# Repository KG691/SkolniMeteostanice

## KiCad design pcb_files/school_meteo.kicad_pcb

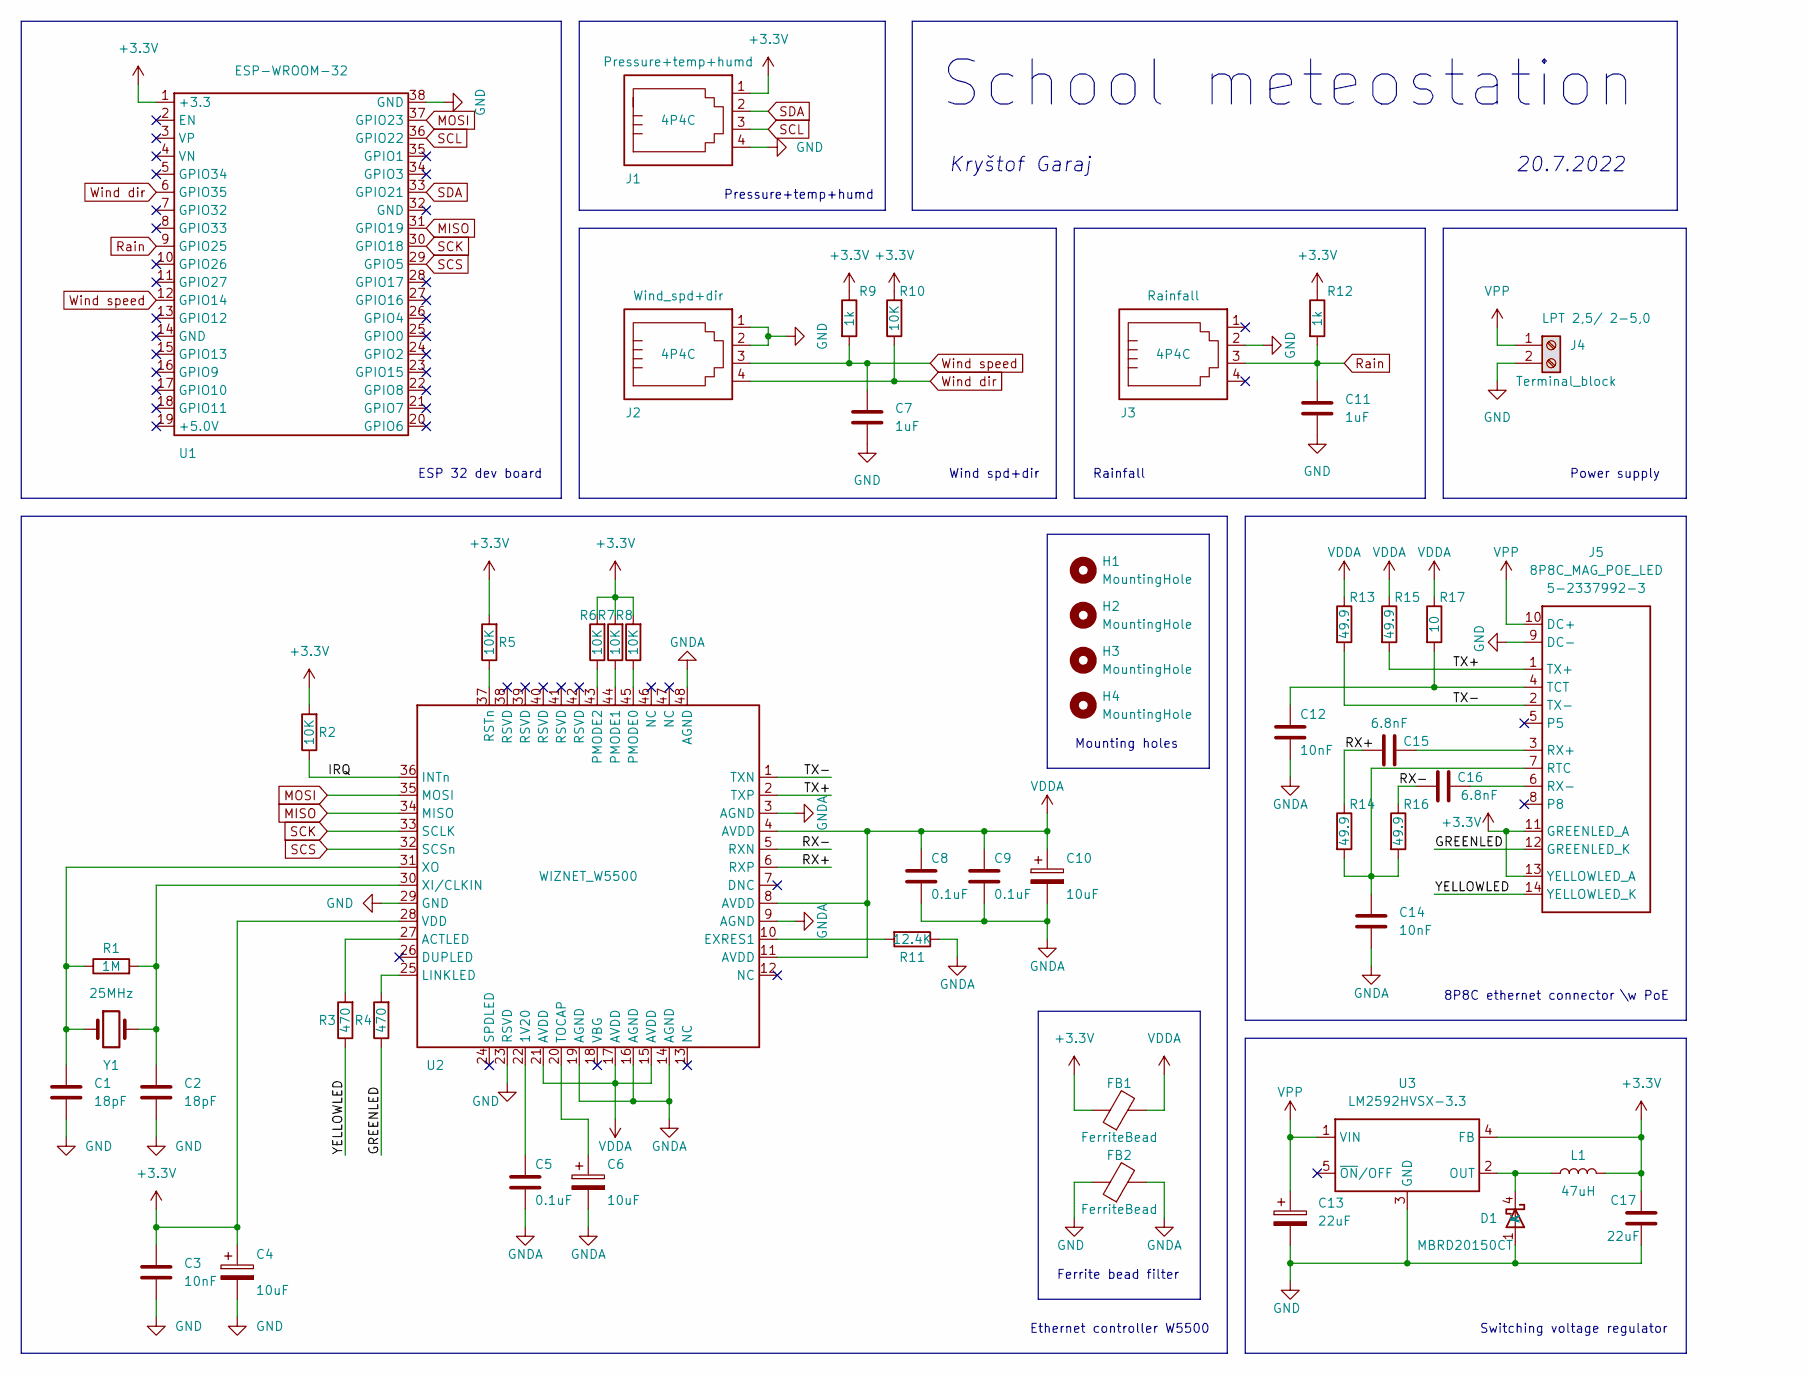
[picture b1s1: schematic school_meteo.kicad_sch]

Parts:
C1, C2: 18pF; C_Rect_L4.6mm_W3.0mm_P2.50mm_MKS02_FKP02
C3, C12, C14: 10nF; C_Rect_L4.6mm_W3.0mm_P2.50mm_MKS02_FKP02
C4, C6, C10: 10uF; CP_Radial_D5.0mm_P2.00mm
C5, C8, C9: 0.1uF; C_Rect_L4.6mm_W3.0mm_P2.50mm_MKS02_FKP02
C7, C11: 1uF; C_Rect_L4.6mm_W3.8mm_P2.50mm_MKS02_FKP02
C13: 22uF; CP_Radial_D6.3mm_P2.50mm
C15, C16: 6.8nF; C_Rect_L4.6mm_W3.0mm_P2.50mm_MKS02_FKP02
C17: 22uF; C_Rect_L4.6mm_W3.0mm_P2.50mm_MKS02_FKP02
D1: MBRD20150CT; TO-252-3_TabPin4
FB1, FB2: FerriteBead; Ferrite_bead_0805
H1, H2, H3, H4: MountingHole; MountingHole_3.2mm_M3_DIN965_Pad
J1, J2, J3: 4P4C
J4: Terminal_block; Phoenix_LPT_2,5_2-5,0
J5: 8P8C_MAG_POE_LED; TE_Connectivity_PoE
L1: 47uH; L_12x12mm_H8mm
R1: 1M; R_Axial_DIN0204_L3.6mm_D1.6mm_P5.08mm_Horizontal
R2, R5, R6, R7, R8, R10: 10K; R_Axial_DIN0204_L3.6mm_D1.6mm_P5.08mm_Horizontal
R3, R4: 470; R_Axial_DIN0204_L3.6mm_D1.6mm_P5.08mm_Horizontal
R9, R12: 1k; R_Axial_DIN0204_L3.6mm_D1.6mm_P5.08mm_Horizontal
R11: 12.4K; R_Axial_DIN0207_L6.3mm_D2.5mm_P7.62mm_Horizontal
R13, R14, R15, R16: 49.9; R_Axial_DIN0207_L6.3mm_D2.5mm_P7.62mm_Horizontal
R17: 10; R_Axial_DIN0207_L6.3mm_D2.5mm_P7.62mm_Horizontal
U1: ESP-WROOM-32
U2: WIZNET_W5500; LQFP-48_7x7mm_P0.5mm
U3: LM2592HVSX-3.3; TO-263-5_TabPin3
Y1: 25MHz; Crystal_HC49-U_Vertical

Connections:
+3V3: C3.1, C4.1, C17.2, FB1.1, J1.1, J5.11 (GREENLED_A), J5.13 (YELLOWLED_A), L1.2, R2.2, R5.2, R6.2, R7.2, R8.2, R9.1, R10.2, R12.1, U1.1 (+3.3), U2.28 (VDD), U3.4 (FB)
/GREENLED: J5.12 (GREENLED_K), R4.1
/IRQ: R2.1, U2.36 (INTn)
/RX+: C15.1, R14.1, U2.6 (RXP)
/RX-: C16.1, R16.1, U2.5 (RXN)
/TX+: J5.1 (TX+), R15.2, U2.2 (TXP)
/TX-: J5.2 (TX-), R13.2, U2.1 (TXN)
/YELLOWLED: J5.14 (YELLOWLED_K), R3.1
GND: C1.2, C2.2, C3.2, C4.2, C7.2, C11.2, C13.2, C17.1, D1.1 (A), FB2.1, J1.4, J2.1, J2.2, J3.2, J4.2, J5.9 (DC-), U1.38 (GND), U2.23 (RSVD), U2.29 (GND), U3.3 (GND)
GNDA: C5.2, C6.2, C8.2, C9.2, C10.2, C12.2, C14.2, FB2.2, R11.1, U2.3 (AGND), U2.9 (AGND), U2.14 (AGND), U2.16 (AGND), U2.19 (AGND), U2.48 (AGND)
MISO: U1.31 (GPIO19), U2.34 (MISO)
MOSI: U1.37 (GPIO23), U2.35 (MOSI)
unnamed: C1.1, R1.1, U2.31 (XO), Y1.1
unnamed: C2.1, R1.2, U2.30 (XI/CLKIN), Y1.2
unnamed: C5.1, U2.22 (1V20)
unnamed: C6.1, U2.20 (TOCAP)
unnamed: C12.1, J5.4 (TCT), R17.2
unnamed: C14.1, J5.7 (RTC), R14.2, R16.2
unnamed: C15.2, J5.3 (RX+)
unnamed: C16.2, J5.6 (RX-)
unnamed: D1.4 (K), L1.1, U3.2 (OUT)
unnamed: R3.2, U2.27 (ACTLED)
unnamed: R4.2, U2.25 (LINKLED)
unnamed: R5.1, U2.37 (RSTn)
unnamed: R6.1, U2.43 (PMODE2)
unnamed: R7.1, U2.44 (PMODE1)
unnamed: R8.1, U2.45 (PMODE0)
unnamed: R11.2, U2.10 (EXRES1)
Rain: C11.1, J3.3, R12.2, U1.9 (GPIO25)
SCK: U1.30 (GPIO18), U2.33 (SCLK)
SCL: J1.3, U1.36 (GPIO22)
SCS: U1.29 (GPIO5), U2.32 (SCSn)
SDA: J1.2, U1.33 (GPIO21)
VDDA: C8.1, C9.1, C10.1, FB1.2, R13.1, R15.1, R17.1, U2.4 (AVDD), U2.8 (AVDD), U2.11 (AVDD), U2.15 (AVDD), U2.17 (AVDD), U2.21 (AVDD)
VPP: C13.1, J4.1, J5.10 (DC+), U3.1 (VIN)
Wind dir: J2.4, R10.1, U1.6 (GPIO35)
Wind speed: C7.1, J2.3, R9.2, U1.12 (GPIO14)

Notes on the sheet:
8P8C ethernet connector \w PoE
Kryštof Garaj
Wind spd+dir
Pressure+temp+humd
Power supply
Ferrite bead filter
Mounting holes
Ethernet controller W5500
Rainfall
Switching voltage regulator
School meteostation
ESP 32 dev board
20.7.2022

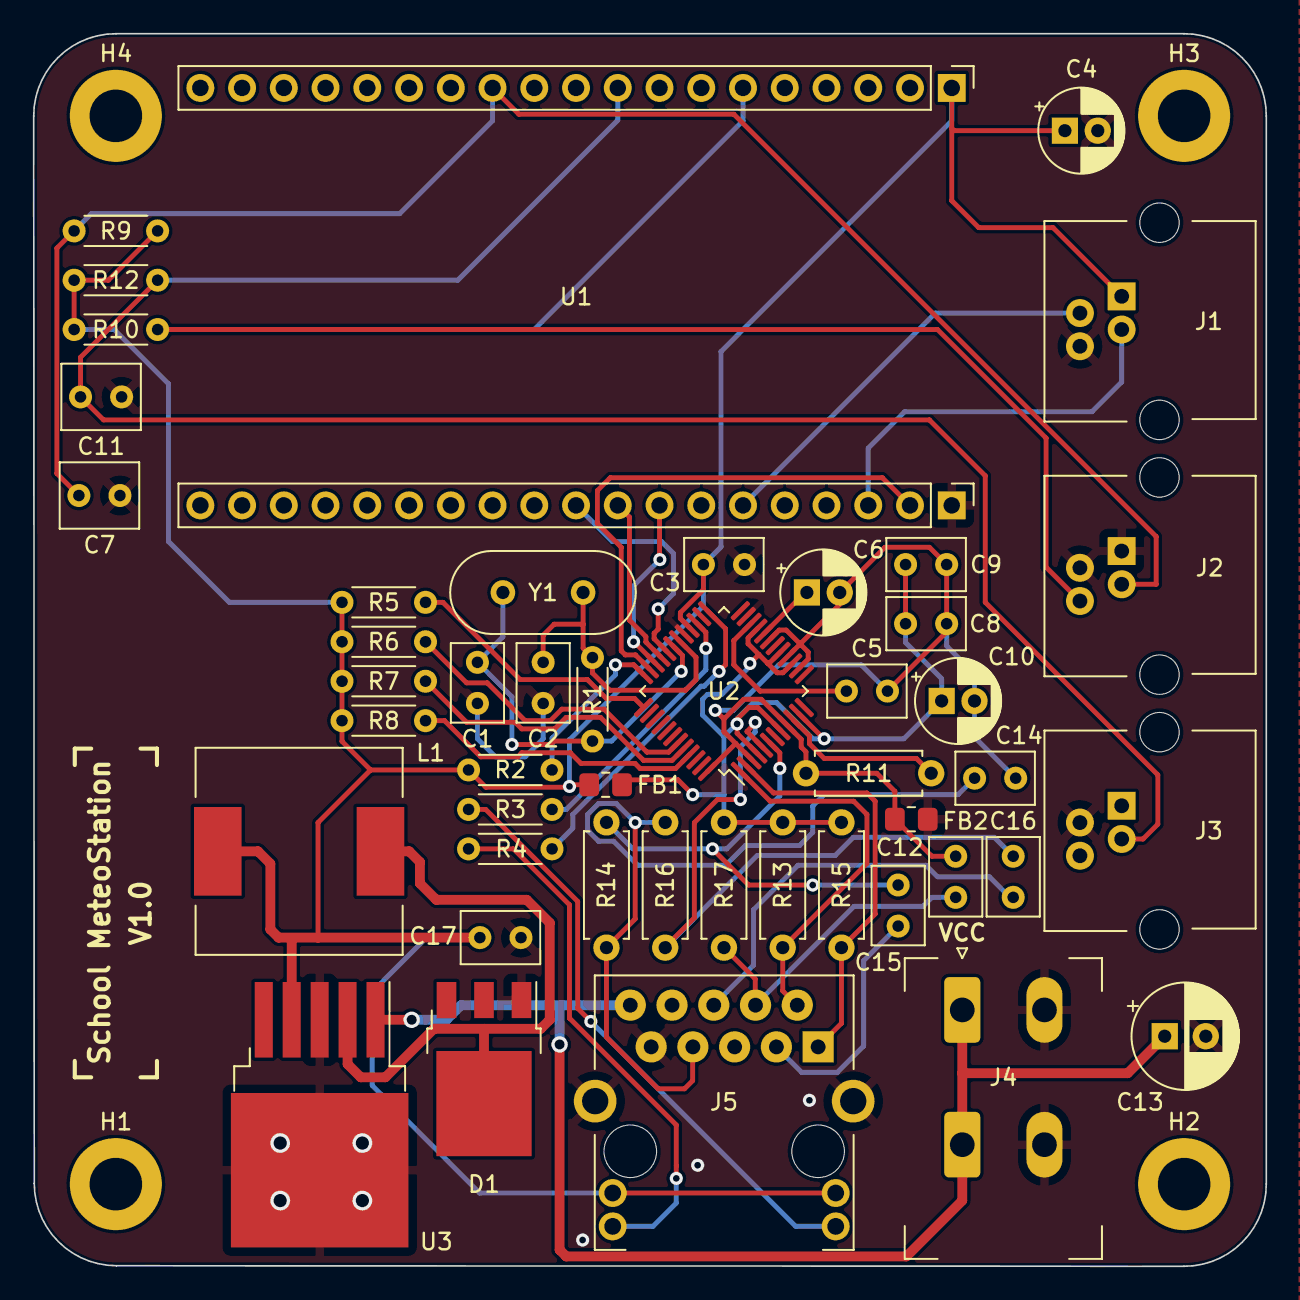
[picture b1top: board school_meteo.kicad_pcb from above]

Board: 2 copper layers, 75.0 x 75.0 mm, 51 parts (0 on the bottom side), 37 nets.

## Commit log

2022-07-09 Changing the table for the wind direction
    Changing the table for the wind direction, since the old one was flipped
2022-07-27 Create pcb_files
2022-07-27 Update SchoolMeteo.ino
    MInor changes in code
2022-07-27 Create school_meteo.kicad_sch
    Adding KiCad schematic
2022-07-31 Correction of grammatical errors
    Correction of grammatical errors in documentation
2022-08-02 Adding BOM
    Creating BOM with designators, values, types, IDs, links and prices of the parts
2022-08-02 Updating BOM
    Adding some parts
2022-08-02 Updating schematic
    Updating schematic
2022-08-02 Adding pcb layout
    Adding pcb layout
2022-08-09 Minor changes
    Adding back accidentaly deleted line
2022-08-09 Minor changes
    Reverting unwanted changes
2022-08-10 Adding the library used for MQTT
    Adding the library PubSubCient in the version used in my project. Also including a link for download
2022-08-10 Adding a link for download of library used for MQTT
    Adding a link for download of library used for MQTT
2022-08-10 Making the usage of MQTT easier
    Using MQTT now requires a change of 2 lines of code
2022-08-15 I2C and ESP32 better explanation
    Adding a more indepth explanation of how I2C works
2022-08-15 Adding the list of pictures and tables
    Adding the list of pictures and tables
2022-08-15 Adding abstract in english and labeling pictures
    Adding abstract in english and labeling pictures
2022-08-15 Explaining how to use the meteostation
    Adding a better explanation on how to use the meteostation and how to folow my steps to make on from scratch.
2022-08-16 Adding MQTT explanation and manual
    Adding mqtt explanation and paragraph on how to use the meteostation and paragraph on where to place the meteostation
2022-08-18 Change of temp+hum sensor for HTU21D GY-21
    Change of temp+hum sensor for HTU21D GY-21 to utilize I2C
2022-08-18 Adding unit for pressure
    Adding tested unit for pressure
2022-08-18 Adding a unit for pressure , humidity and temperature
    Adding a tested unit for pressure , humidity and temperature
2022-08-18 Adding unit for rainfall
    Adding tested unit for rainfall
2022-08-18 Adding unit for temperature and humidity
    Adding tested unit for temperature and humidity
2022-08-18 Adding unit for wind speed
    Adding tested unit for temperature and humidity
2022-08-18 Adding unit for wind speed and direction
    Adding tested unit for wind speed and direction
2022-08-18 Making MQTT setup easier
    Making MQTT setup posible with chang of four lines of code
2022-08-21 Remov
2022-08-21 Deleting accidentaly added file because of name issue
    Deleting accidentaly added file because of name issue
2022-08-21 Removing code used for DHT sensor
    Removing code used for DHT sensor because I'm using HTU21D GY-21 instead
2022-08-21 Adding how I implemented ethernet and POE
    Adding how I implemented ethernet and POE
2022-08-22 Adding gerber files
    Adding gerber files for the pcb
2022-08-22 This library is not needed
    This library is not needed because I'm using a different sensor
2022-08-22 Adding library for the new sensor
    Adding library for the new sensor of temperature and humidity HTU21D
2022-08-22 Adding the link of the GyverHTU21D library
    Adding the link of the GyverHTU21D library for temperature and humidity
2022-08-22 Changes in descriptions of chapters and other minor changes
    Changes in descriptions of chapters and other minor changes
